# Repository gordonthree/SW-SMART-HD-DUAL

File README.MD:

# Heavy Duty Dual Smart Switch Node

Compact power distribution module intended to control two heavy duty high-side DC loads. The module provides eFuse protection and current monitoring for each load. Module temperature and supply voltage are also monitored. This module works with other CAN-CTL modules using the robust CAN bus interface.

<IMG src="https://github.com/gordonthree/SW-SMART-HD-DUAL/blob/main/SW-SMART-HD-DUAL.png?raw=true" width=480>

* STM32G0B1KBT 32-pin microcontroller on board
* Dual Infineon BTS50010 Profet smart switches for high side loads
* Microchip MCP2562 isolated CAN bus transceiver
* Voltage divider to monitor supply voltage
* High side switch current monitoring and diagnostics
* Three position screw terminal block for CAN bus connection
* Heavy duty terminal block connectors for power in/out
* Headers for SWD programming and USART1 debug serial port

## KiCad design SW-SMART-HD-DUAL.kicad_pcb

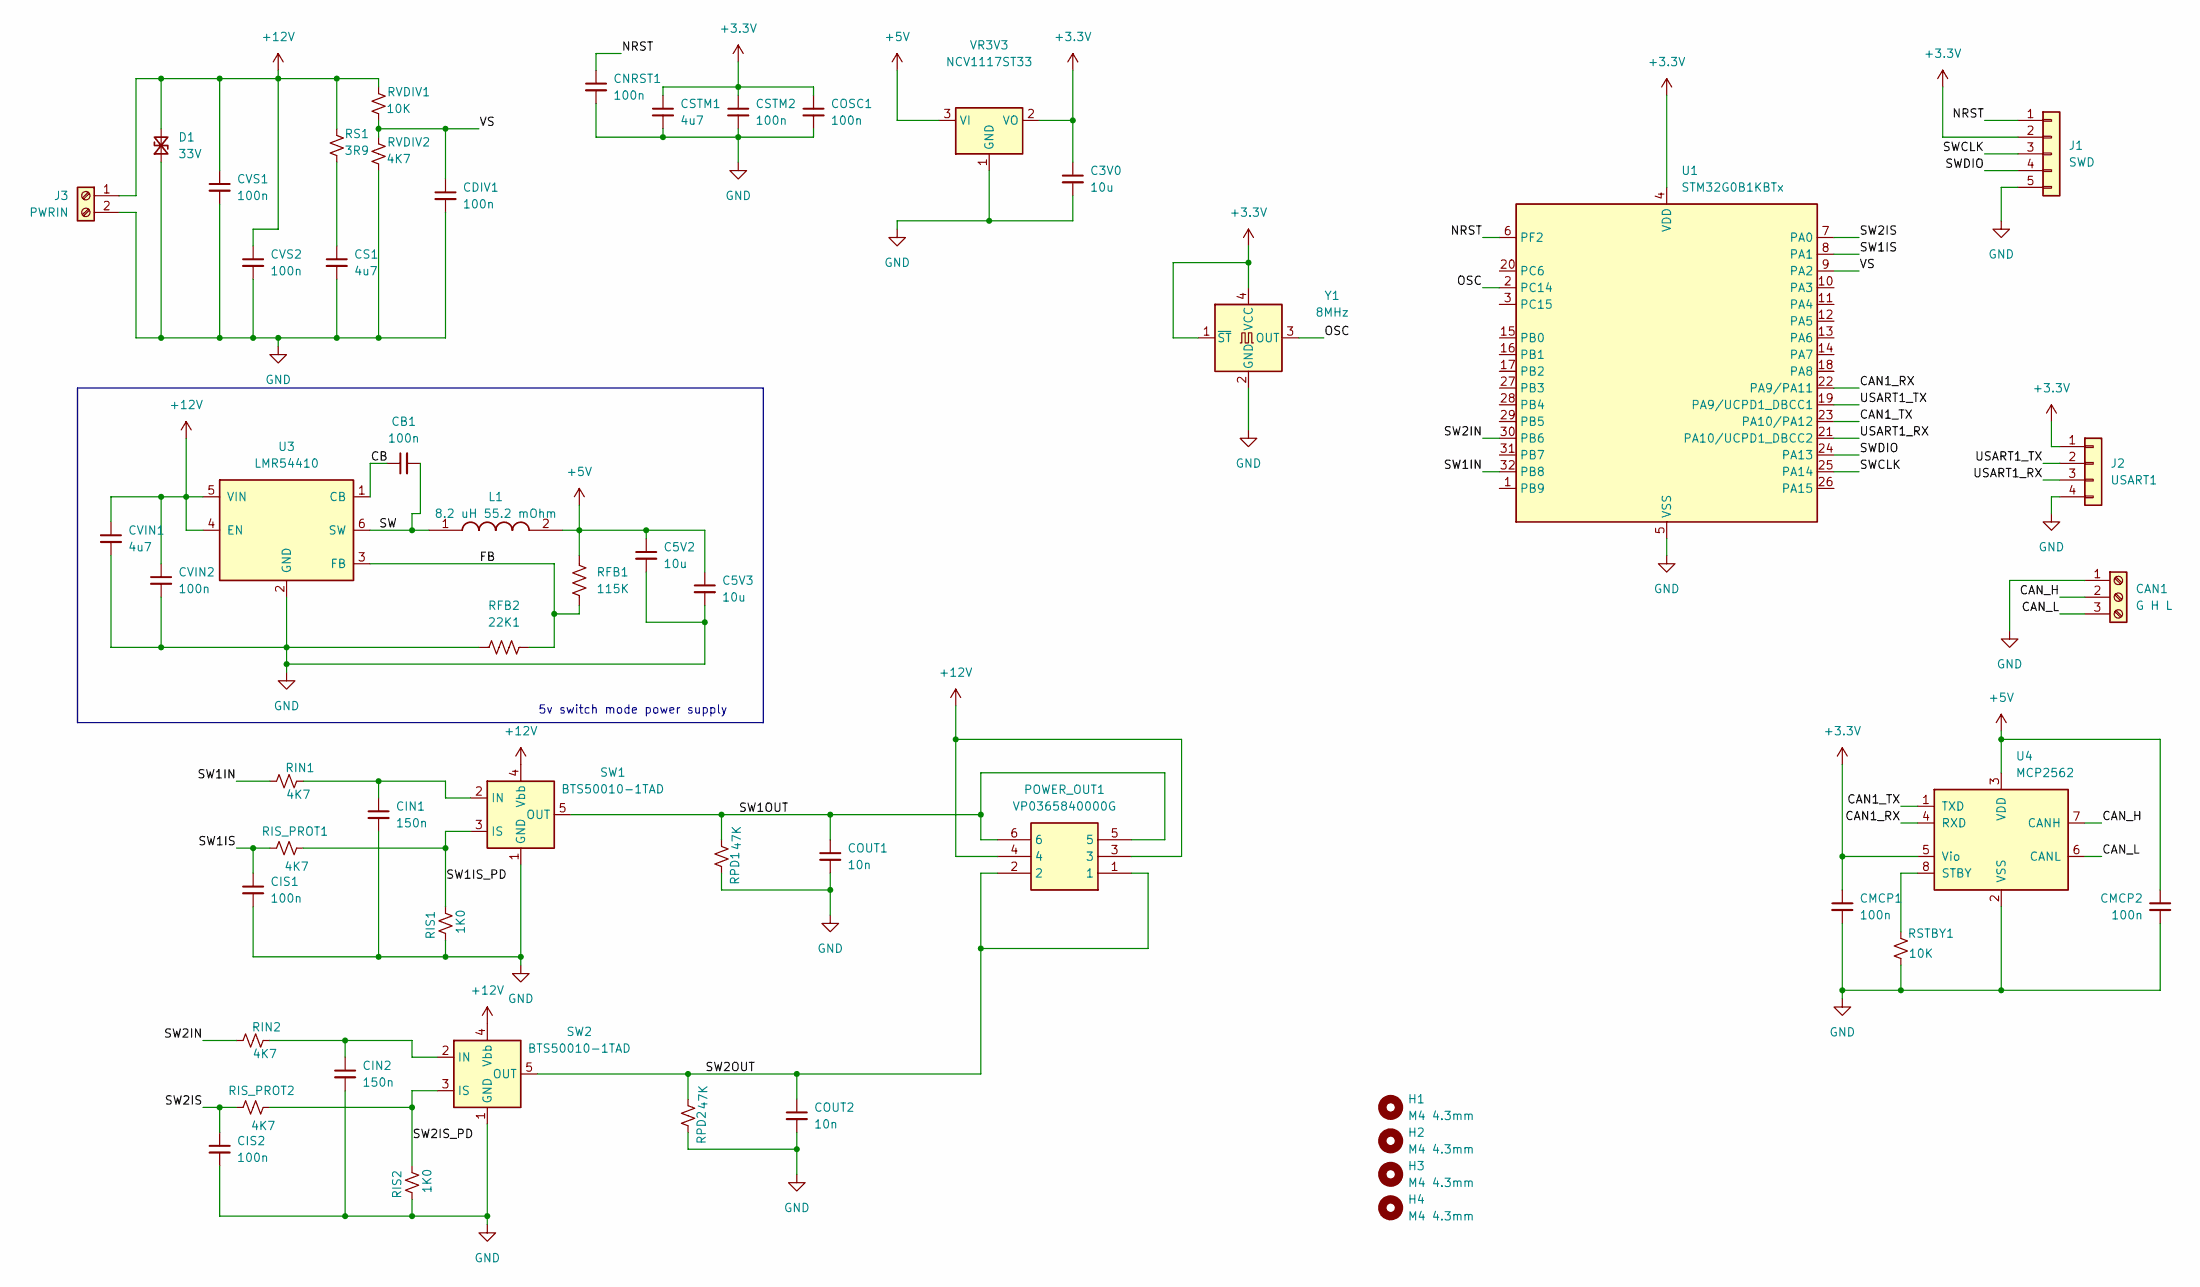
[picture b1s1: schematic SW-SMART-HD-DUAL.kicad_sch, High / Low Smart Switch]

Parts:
C3V0, C5V2, C5V3: 10u; C_0805_2012Metric_Pad1.18x1.45mm_HandSolder
CAN1: G H L; TerminalBlock_Phoenix_MPT-0,5-3-2.54_1x03_P2.54mm_Horizontal
CB1: 100n; C_0603_1608Metric_Pad1.08x0.95mm_HandSolder
CDIV1: 100n; C_0603_1608Metric_Pad1.08x0.95mm_HandSolder
CIN1, CIN2: 150n; C_0603_1608Metric_Pad1.08x0.95mm_HandSolder
CIS1, CIS2: 100n; C_0603_1608Metric_Pad1.08x0.95mm_HandSolder
CMCP1, CMCP2: 100n; C_0603_1608Metric_Pad1.08x0.95mm_HandSolder
CNRST1: 100n; C_0603_1608Metric_Pad1.08x0.95mm_HandSolder
COSC1: 100n; C_0603_1608Metric_Pad1.08x0.95mm_HandSolder
COUT1, COUT2: 10n; C_0603_1608Metric_Pad1.08x0.95mm_HandSolder
CS1: 4u7; C_0603_1608Metric_Pad1.08x0.95mm_HandSolder
CSTM1: 4u7; C_0805_2012Metric_Pad1.18x1.45mm_HandSolder
CSTM2: 100n; C_0603_1608Metric_Pad1.08x0.95mm_HandSolder
CVIN1: 4u7; C_1210_3225Metric_Pad1.33x2.70mm_HandSolder
CVIN2: 100n; C_0603_1608Metric_Pad1.08x0.95mm_HandSolder
CVS1, CVS2: 100n; C_0603_1608Metric_Pad1.08x0.95mm_HandSolder
D1: 33V; D_SMA_Handsoldering
H1, H2, H3, H4: M4 4.3mm; MountingHole_4.3mm_M4
J1: SWD; PinHeader_1x05_P2.54mm_Vertical
J2: USART1; PinHeader_1x04_P2.54mm_Vertical
J3: PWRIN; TerminalBlock_Phoenix_MPT-0,5-2-2.54_1x02_P2.54mm_Horizontal
L1: 8.2 uH 55.2 mOhm; SRP5030HMT2R2M; Mouser Part Number SRP5030HMT-8R2M
POWER_OUT1: VP0365840000G; Mouser Part Number 649-VP03658400J0G
RFB1: 115K; R_0603_1608Metric_Pad0.98x0.95mm_HandSolder
RFB2: 22K1; R_0603_1608Metric_Pad0.98x0.95mm_HandSolder
RIN1, RIN2: 4K7; R_0603_1608Metric_Pad0.98x0.95mm_HandSolder
RIS1, RIS2: 1K0; R_0603_1608Metric_Pad0.98x0.95mm_HandSolder
RIS_PROT1, RIS_PROT2: 4K7; R_0603_1608Metric_Pad0.98x0.95mm_HandSolder
RPD1, RPD2: 47K; R_0603_1608Metric_Pad0.98x0.95mm_HandSolder
RS1: 3R9; R_0603_1608Metric_Pad0.98x0.95mm_HandSolder
RSTBY1: 10K; R_0603_1608Metric_Pad0.98x0.95mm_HandSolder
RVDIV1: 10K; R_0603_1608Metric_Pad0.98x0.95mm_HandSolder
RVDIV2: 4K7; R_0603_1608Metric_Pad0.98x0.95mm_HandSolder
SW1, SW2: BTS50010-1TAD; TO-263-7_TabPin4
U1: STM32G0B1KBTx; LQFP-32_7x7mm_P0.8mm
U3: LMR54410; SOT-23-6
U4: MCP2562; SOIC-8_3.9x4.9mm_P1.27mm
VR3V3: NCV1117ST33; SOT-223-3_TabPin2
Y1: 8MHz; Oscillator_SMD_EuroQuartz_XO32-4Pin_3.2x2.5mm_RotB_HandSold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

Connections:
+3.3V: C3V0.1, CMCP1.1, COSC1.1, CSTM1.1, CSTM2.1, J1.2, J2.1, U1.4 (VDD), U4.5 (Vio), VR3V3.2 (VO), Y1.1 (~ST), Y1.4 (VCC)
+5V: C5V2.1, C5V3.1, CMCP2.1, L1.2, RFB1.1, U4.3 (VDD), VR3V3.3 (VI)
+12V: CVIN1.1, CVIN2.1, CVS1.1, CVS2.1, D1.2 (A2), J3.1, POWER_OUT1.3, POWER_OUT1.4, RS1.2, RVDIV1.2, SW1.4 (Vbb), SW2.4 (Vbb), U3.4 (EN), U3.5 (VIN)
/CAN1_RX: U1.22 (PA9/PA11), U4.4 (RXD)
/CAN1_TX: U1.23 (PA10/PA12), U4.1 (TXD)
/CAN_H: CAN1.2, U4.7 (CANH)
/CAN_L: CAN1.3, U4.6 (CANL)
/CB: CB1.1, U3.1 (CB)
/FB: RFB1.2, RFB2.2, U3.3 (FB)
/NRST: CNRST1.1, J1.1, U1.6 (PF2)
/OSC: U1.2 (PC14), Y1.3 (OUT)
/SW: CB1.2, L1.1, U3.6 (SW)
/SW1IN: RIN1.1, U1.32 (PB8)
/SW1IS: CIS1.1, RIS_PROT1.1, U1.8 (PA1)
/SW1IS_PD: RIS1.2, RIS_PROT1.2, SW1.3 (IS)
/SW1OUT: COUT1.1, POWER_OUT1.5, POWER_OUT1.6, RPD1.2, SW1.5 (OUT), SW1.6 (OUT), SW1.7 (OUT)
/SW2IN: RIN2.1, U1.30 (PB6)
/SW2IS: CIS2.1, RIS_PROT2.1, U1.7 (PA0)
/SW2IS_PD: RIS2.2, RIS_PROT2.2, SW2.3 (IS)
/SW2OUT: COUT2.1, POWER_OUT1.1, POWER_OUT1.2, RPD2.2, SW2.5 (OUT), SW2.6 (OUT), SW2.7 (OUT)
/SWCLK: J1.3, U1.25 (PA14)
/SWDIO: J1.4, U1.24 (PA13)
/USART1_RX: J2.3, U1.21 (PA10/UCPD1_DBCC2)
/USART1_TX: J2.2, U1.19 (PA9/UCPD1_DBCC1)
/VS: CDIV1.1, RVDIV1.1, RVDIV2.2, U1.9 (PA2)
GND: C3V0.2, C5V2.2, C5V3.2, CAN1.1, CDIV1.2, CIN1.2, CIN2.2, CIS1.2, CIS2.2, CMCP1.2, CMCP2.2, CNRST1.2, COSC1.2, COUT1.2, COUT2.2, CS1.2, CSTM1.2, CSTM2.2, CVIN1.2, CVIN2.2, CVS1.2, CVS2.2, D1.1 (A1), J1.5, J2.4, J3.2, RFB2.1, RIS1.1, RIS2.1, RPD1.1, RPD2.1, RSTBY1.1, RVDIV2.1, SW1.1 (GND), SW2.1 (GND), U1.5 (VSS), U3.2 (GND), U4.2 (VSS), VR3V3.1 (GND), Y1.2 (GND)
unnamed: CS1.1, RS1.1
unnamed: CIN1.1, RIN1.2, SW1.2 (IN)
unnamed: CIN2.1, RIN2.2, SW2.2 (IN)
unnamed: RSTBY1.2, U4.8 (STBY)

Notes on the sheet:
5v switch mode power supply

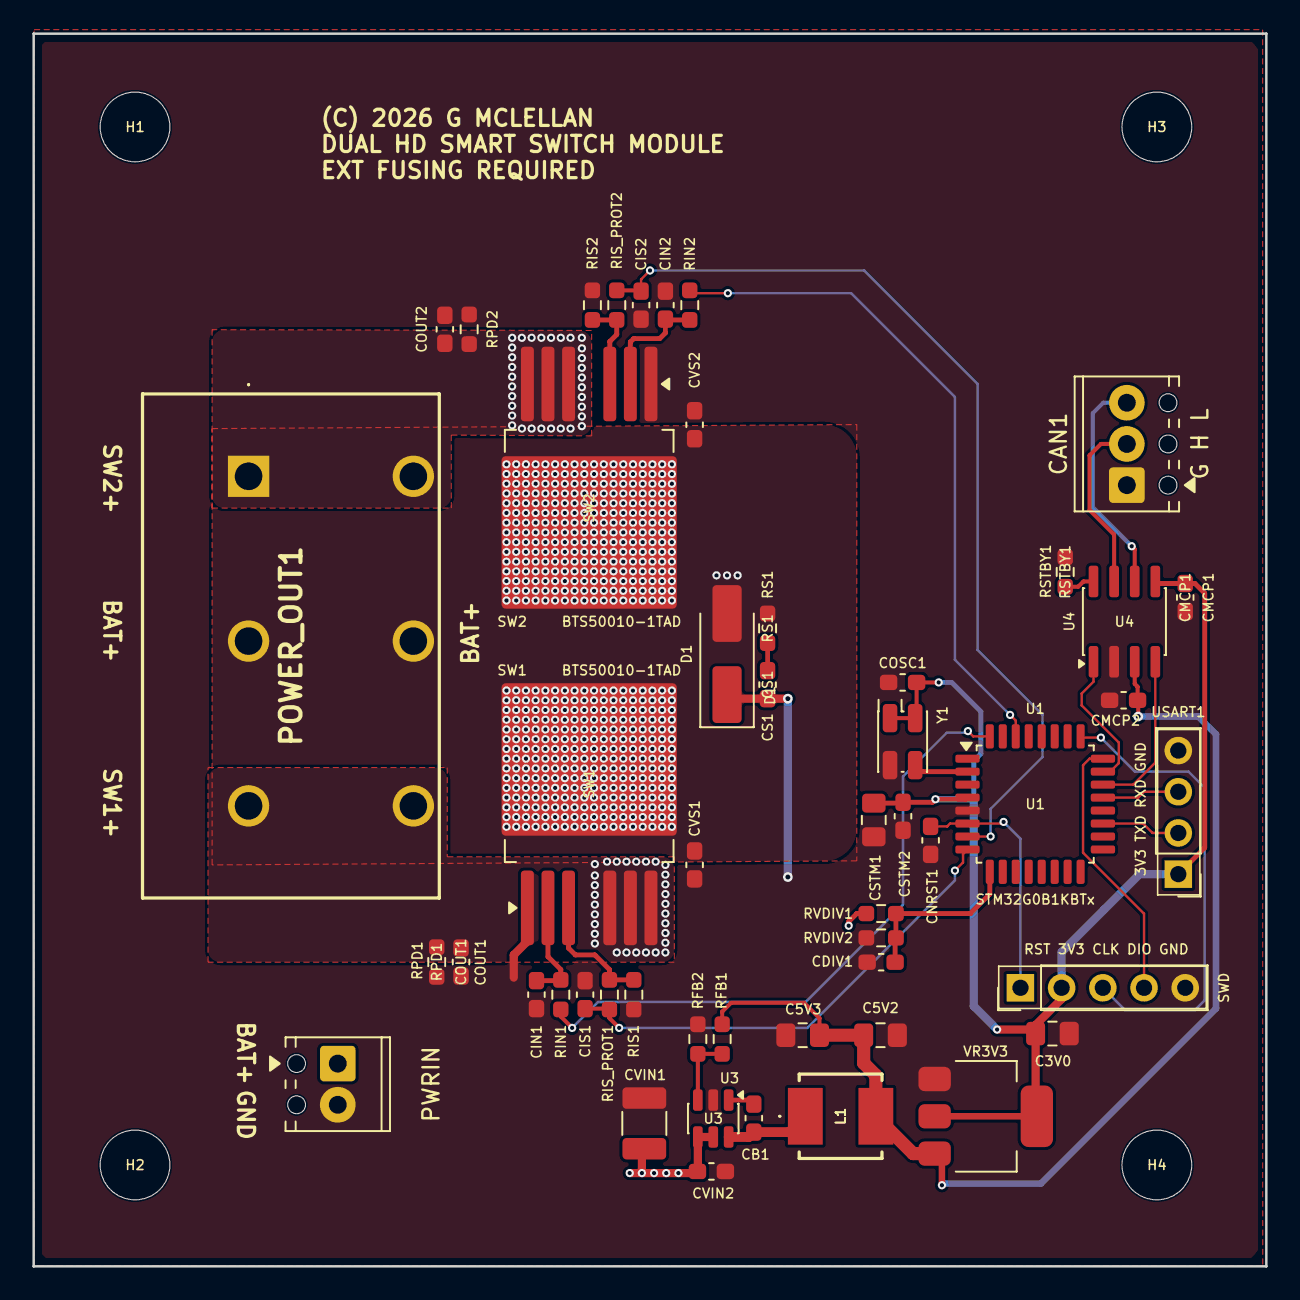
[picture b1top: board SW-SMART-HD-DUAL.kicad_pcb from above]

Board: 2 copper layers, 76.0 x 76.0 mm, 54 parts (0 on the bottom side), 30 nets.

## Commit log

2026-01-30 lots of updates
2026-01-30 update module name
2026-01-31 updated rendering
2026-01-31 layout complete, drc passed
2026-01-31 github not recognizing updated rendering
2026-01-31 embedded image
2026-02-02 update rendering to include new XO
2026-02-02 added crystal osc, fixed some silkscreen issues, moved a few tracks
2026-02-02 moved osc capacitor for easier copy pasta

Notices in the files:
SW-SMART-HD-DUAL.kicad_pcb:
(C) 2026 G MCLELLAN
